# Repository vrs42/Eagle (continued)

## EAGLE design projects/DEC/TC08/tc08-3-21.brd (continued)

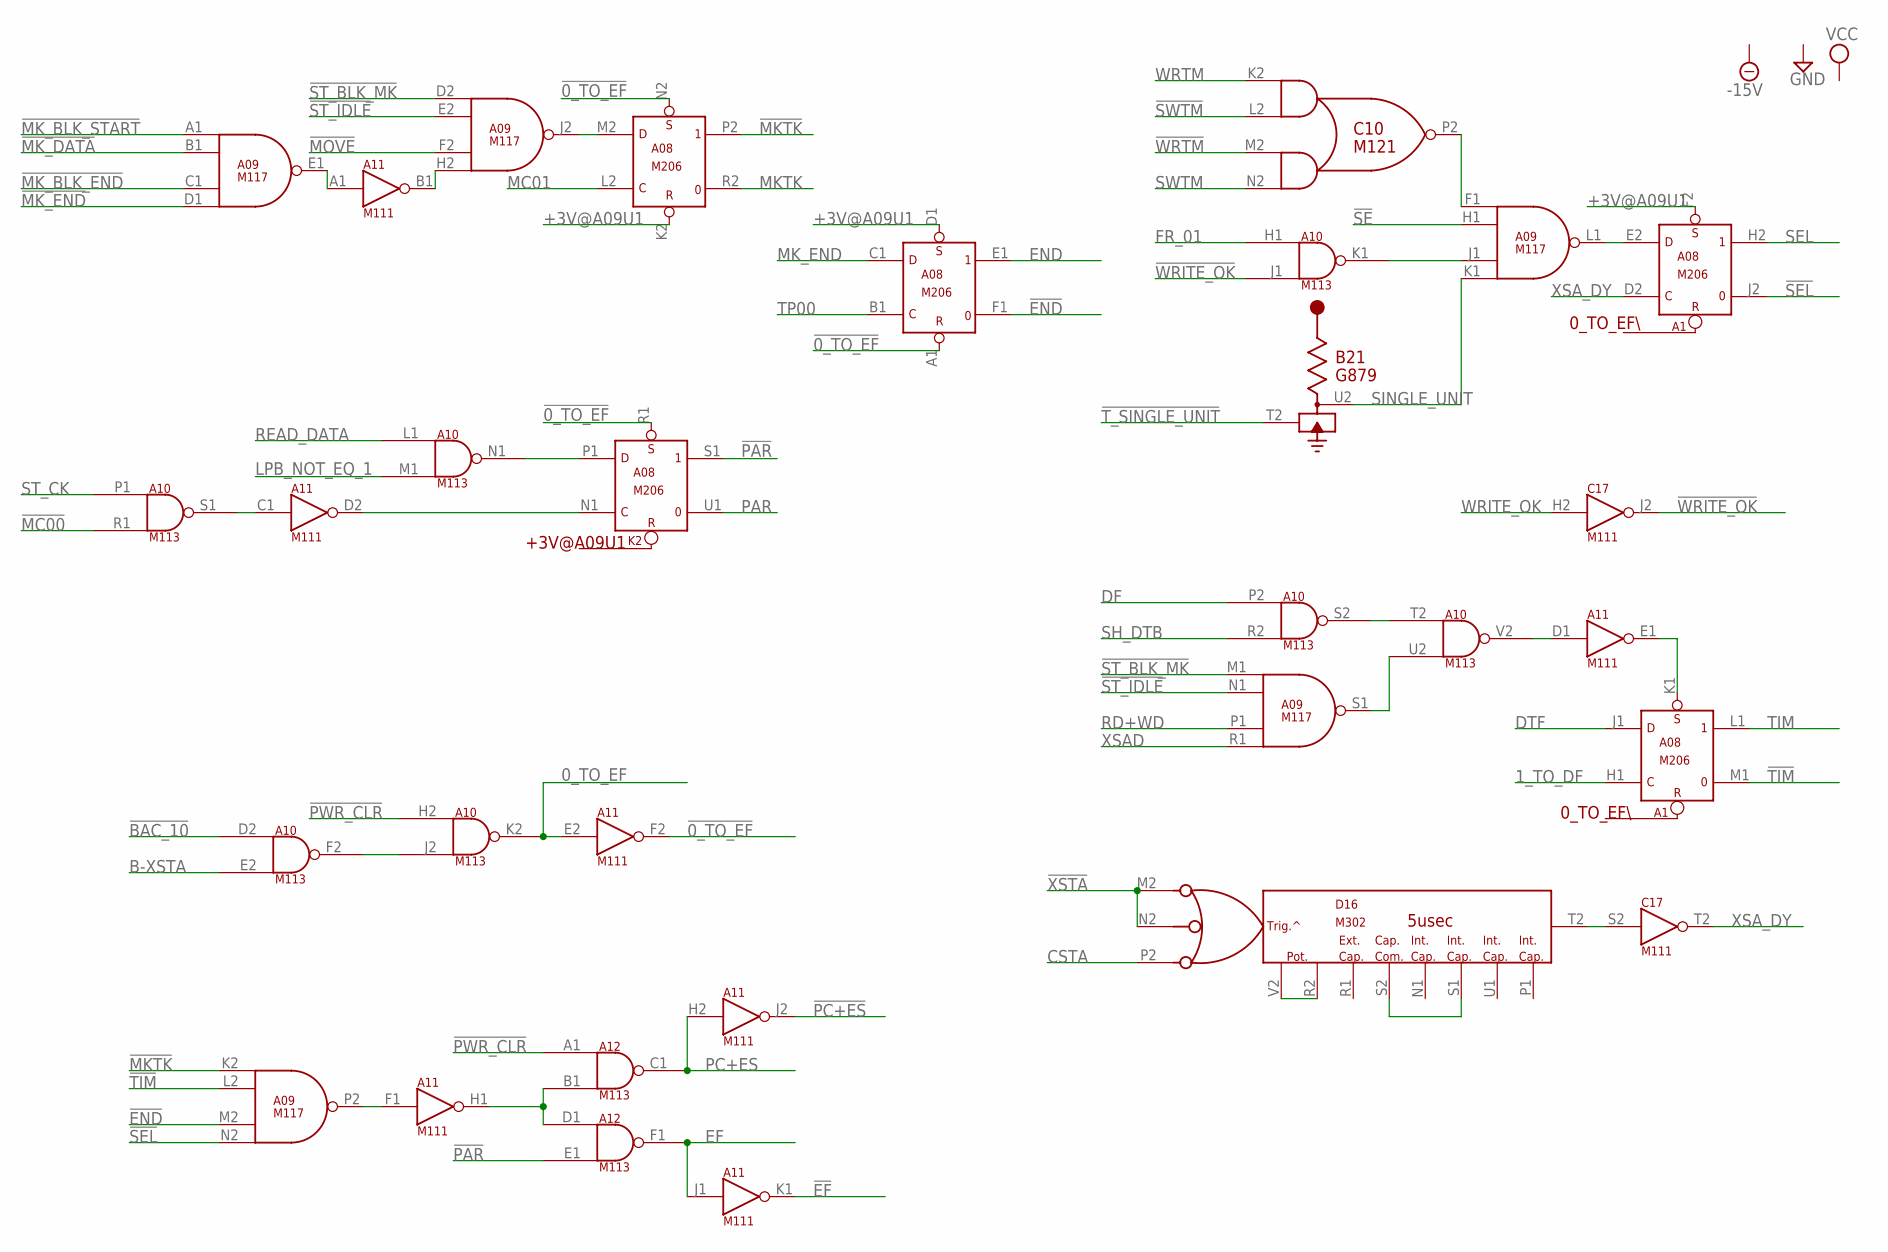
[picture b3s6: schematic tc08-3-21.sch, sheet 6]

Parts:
A08: M206; H807
A09: M117; H807
A10, A12: M113; H807
A11: M111; H807
B21: G879; H807
C10: M121; H807
C17: M111; H807
D16: M302; H807

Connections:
0_TO_EF: A10.K2 (OUT), A11.E2 (IN)
1_TO_DF: A08.H1 (C); also elsewhere on the board
!0_TO_EF: A08.A1 (R), A08.N2 (S), A08.R1 (S), A11.F2 (OUT)
!BAC_10: A10.D2 (IN1); also elsewhere on the board
!EF: A11.K1 (OUT); also elsewhere on the board
!END: A08.F1 (0), A09.M2 (IN3); also elsewhere on the board
!MC00: A10.R1 (IN2); also elsewhere on the board
!MKTK: A08.P2 (1), A09.K2 (IN1); also elsewhere on the board
!MK_BLK_END: A09.C1 (IN3); also elsewhere on the board
!MK_BLK_START: A09.A1 (IN1); also elsewhere on the board
!MK_DATA: A09.B1 (IN2); also elsewhere on the board
!MK_END: A09.D1 (IN4); also elsewhere on the board
!MOVE: A09.F2 (IN3); also elsewhere on the board
!PAR: A08.S1 (1), A12.E1 (IN2); also elsewhere on the board
!PC+ES: A11.J2 (OUT); also elsewhere on the board
!PWR_CLR: A10.H2 (IN1), A12.A1 (IN1); also elsewhere on the board
!SE: A09.H1 (IN2); also elsewhere on the board
!SEL: A08.J2 (0), A09.N2 (IN4); also elsewhere on the board
!ST_BLK_MK: A09.D2 (IN1), A09.M1 (IN1); also elsewhere on the board
!ST_IDLE: A09.E2 (IN2), A09.N1 (IN2); also elsewhere on the board
!SWTM: C10.L2 (IN1B); also elsewhere on the board
!TIM: A08.M1 (0), A09.L2 (IN2); also elsewhere on the board
!T_SINGLE_UNIT: B21.T2 (IN); also elsewhere on the board
!WRITE_OK: A10.J1 (IN2), C17.J2 (OUT)
!WRTM: C10.M2 (IN2A); also elsewhere on the board
!XSTA: D16.M2 (H2), D16.N2 (J2); also elsewhere on the board
+3V@A09U1: A08.D1 (S), A08.F2 (S), A08.K2 (R); also elsewhere on the board
-15V: B21.B2 (-15V); also elsewhere on the board
B-XSTA: A10.E2 (IN2); also elsewhere on the board
CSTA: D16.P2 (K2); also elsewhere on the board
DF: A10.P2 (IN1); also elsewhere on the board
DTF: A08.J1 (D); also elsewhere on the board
EF: A11.J1 (IN), A12.F1 (OUT); also elsewhere on the board
END: A08.E1 (1); also elsewhere on the board
FR_01: A10.H1 (IN1); also elsewhere on the board
GND: A08.C2 (GND), A08.T1 (GND), A09.C2 (GND), A09.T1 (GND), A10.C2 (GND), A10.T1 (GND), A11.C2 (GND), A11.T1 (GND), A12.C2 (GND), A12.T1 (GND), B21.C2 (GND), C10.C2 (GND), C10.T1 (GND), C17.C2 (GND), C17.T1 (GND), D16.C2 (GND), D16.T1 (GND); also elsewhere on the board
LPB_NOT_EQ_1: A10.M1 (IN2); also elsewhere on the board
MC01: A08.L2 (C); also elsewhere on the board
MKTK: A08.R2 (0); also elsewhere on the board
MK_END: A08.C1 (D); also elsewhere on the board
unnamed: C17.S2 (IN), D16.T2 (F2)
unnamed: A09.F1 (IN1), C10.P2 (OUT)
unnamed: A09.J1 (IN3), A10.K1 (OUT)
unnamed: A08.E2 (D), A09.L1 (OUT)
unnamed: A09.E1 (OUT), A11.A1 (IN)
unnamed: A09.H2 (IN4), A11.B1 (OUT)
unnamed: A08.M2 (D), A09.J2 (OUT)
unnamed: A10.S1 (OUT), A11.C1 (IN)
unnamed: A08.P1 (D), A10.N1 (OUT)
unnamed: A08.N1 (C), A11.D2 (OUT)
unnamed: A08.K1 (S), A11.E1 (OUT)
unnamed: A10.V2 (OUT), A11.D1 (IN)
unnamed: A09.S1 (OUT), A10.U2 (IN2)
unnamed: A10.S2 (OUT), A10.T2 (IN1)
unnamed: D16.S1 (H1), D16.S2 (L2)
unnamed: D16.R2 (E2), D16.V2 (D2)
unnamed: A10.F2 (OUT), A10.J2 (IN2)
unnamed: A09.P2 (OUT), A11.F1 (IN)
unnamed: A11.H1 (OUT), A12.B1 (IN2), A12.D1 (IN1)
PAR: A08.U1 (0); also elsewhere on the board
PC+ES: A11.H2 (IN), A12.C1 (OUT)
RD+WD: A09.P1 (IN3); also elsewhere on the board
READ_DATA: A10.L1 (IN1); also elsewhere on the board
SEL: A08.H2 (1); also elsewhere on the board
SH_DTB: A10.R2 (IN2); also elsewhere on the board
SINGLE_UNIT: A09.K1 (IN4), B21.U2 (OUT)
ST_CK: A10.P1 (IN1); also elsewhere on the board
SWTM: C10.N2 (IN2B); also elsewhere on the board
TIM: A08.L1 (1); also elsewhere on the board
TP00: A08.B1 (C); also elsewhere on the board
VCC: A08.A2 (VCC), A09.A2 (VCC), A10.A2 (VCC), A11.A2 (VCC), A12.A2 (VCC), B21.A2 (VCC), C10.A2 (VCC), C17.A2 (VCC), D16.A2 (VCC); also elsewhere on the board
WRITE_OK: C17.H2 (IN); also elsewhere on the board
WRTM: C10.K2 (IN1A); also elsewhere on the board
XSAD: A09.R1 (IN4); also elsewhere on the board
XSA_DY: A08.D2 (C), C17.T2 (OUT); also elsewhere on the board

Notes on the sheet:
5usec
+3V@A09U1
0_TO_EF\\

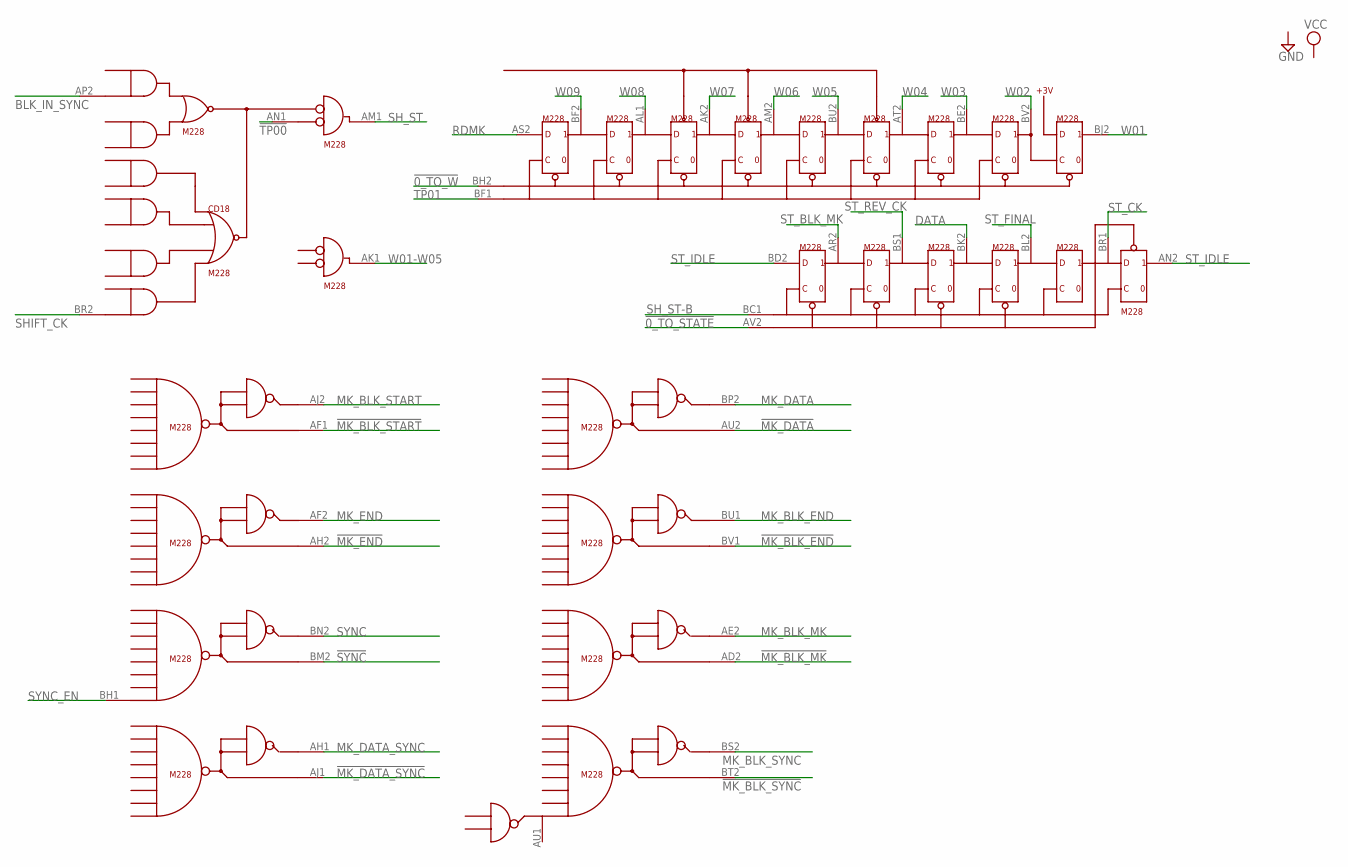
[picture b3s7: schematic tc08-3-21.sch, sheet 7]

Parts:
CD18: M228; H807-2

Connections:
!0_TO_STATE: CD18.AV2; also elsewhere on the board
!0_TO_W: CD18.BH2; also elsewhere on the board
!MK_BLK_END: CD18.BV1; also elsewhere on the board
!MK_BLK_MK: CD18.AD2
!MK_BLK_START: CD18.AF1; also elsewhere on the board
!MK_BLK_SYNC: CD18.BT2
!MK_DATA: CD18.AU2; also elsewhere on the board
!MK_DATA_SYNC: CD18.AJ1
!MK_END: CD18.AH2; also elsewhere on the board
!SYNC: CD18.BM2
!TP00: CD18.AN1; also elsewhere on the board
BLK_IN_SYNC: CD18.AP2; also elsewhere on the board
DATA: CD18.BK2; also elsewhere on the board
GND: CD18.AC2 (GND), CD18.AT1 (GND), CD18.BC2 (GND), CD18.BT1 (GND); also elsewhere on the board
MK_BLK_END: CD18.BU1; also elsewhere on the board
MK_BLK_MK: CD18.AE2; also elsewhere on the board
MK_BLK_START: CD18.AJ2
MK_BLK_SYNC: CD18.BS2
MK_DATA: CD18.BP2
MK_DATA_SYNC: CD18.AH1
MK_END: CD18.AF2; also elsewhere on the board
RDMK: CD18.AS2; also elsewhere on the board
SHIFT_CK: CD18.BR2; also elsewhere on the board
SH_ST: CD18.AM1; also elsewhere on the board
SH_ST-B: CD18.BC1; also elsewhere on the board
ST_BLK_MK: CD18.AR2; also elsewhere on the board
ST_CK: CD18.BR1; also elsewhere on the board
ST_FINAL: CD18.BL2; also elsewhere on the board
ST_IDLE: CD18.AN2, CD18.BD2; also elsewhere on the board
ST_REV_CK: CD18.BS1; also elsewhere on the board
SYNC: CD18.BN2; also elsewhere on the board
SYNC_EN: CD18.BH1; also elsewhere on the board
TP01: CD18.BF1; also elsewhere on the board
VCC: CD18.AA2 (VCC), CD18.BA2 (VCC); also elsewhere on the board
W01: CD18.BJ2; also elsewhere on the board
W01-W05: CD18.AK1
W02: CD18.BV2; also elsewhere on the board
W03: CD18.BE2; also elsewhere on the board
W04: CD18.AT2; also elsewhere on the board
W05: CD18.BU2; also elsewhere on the board
W06: CD18.AM2; also elsewhere on the board
W07: CD18.AK2; also elsewhere on the board
W08: CD18.AL1; also elsewhere on the board
W09: CD18.BF2; also elsewhere on the board

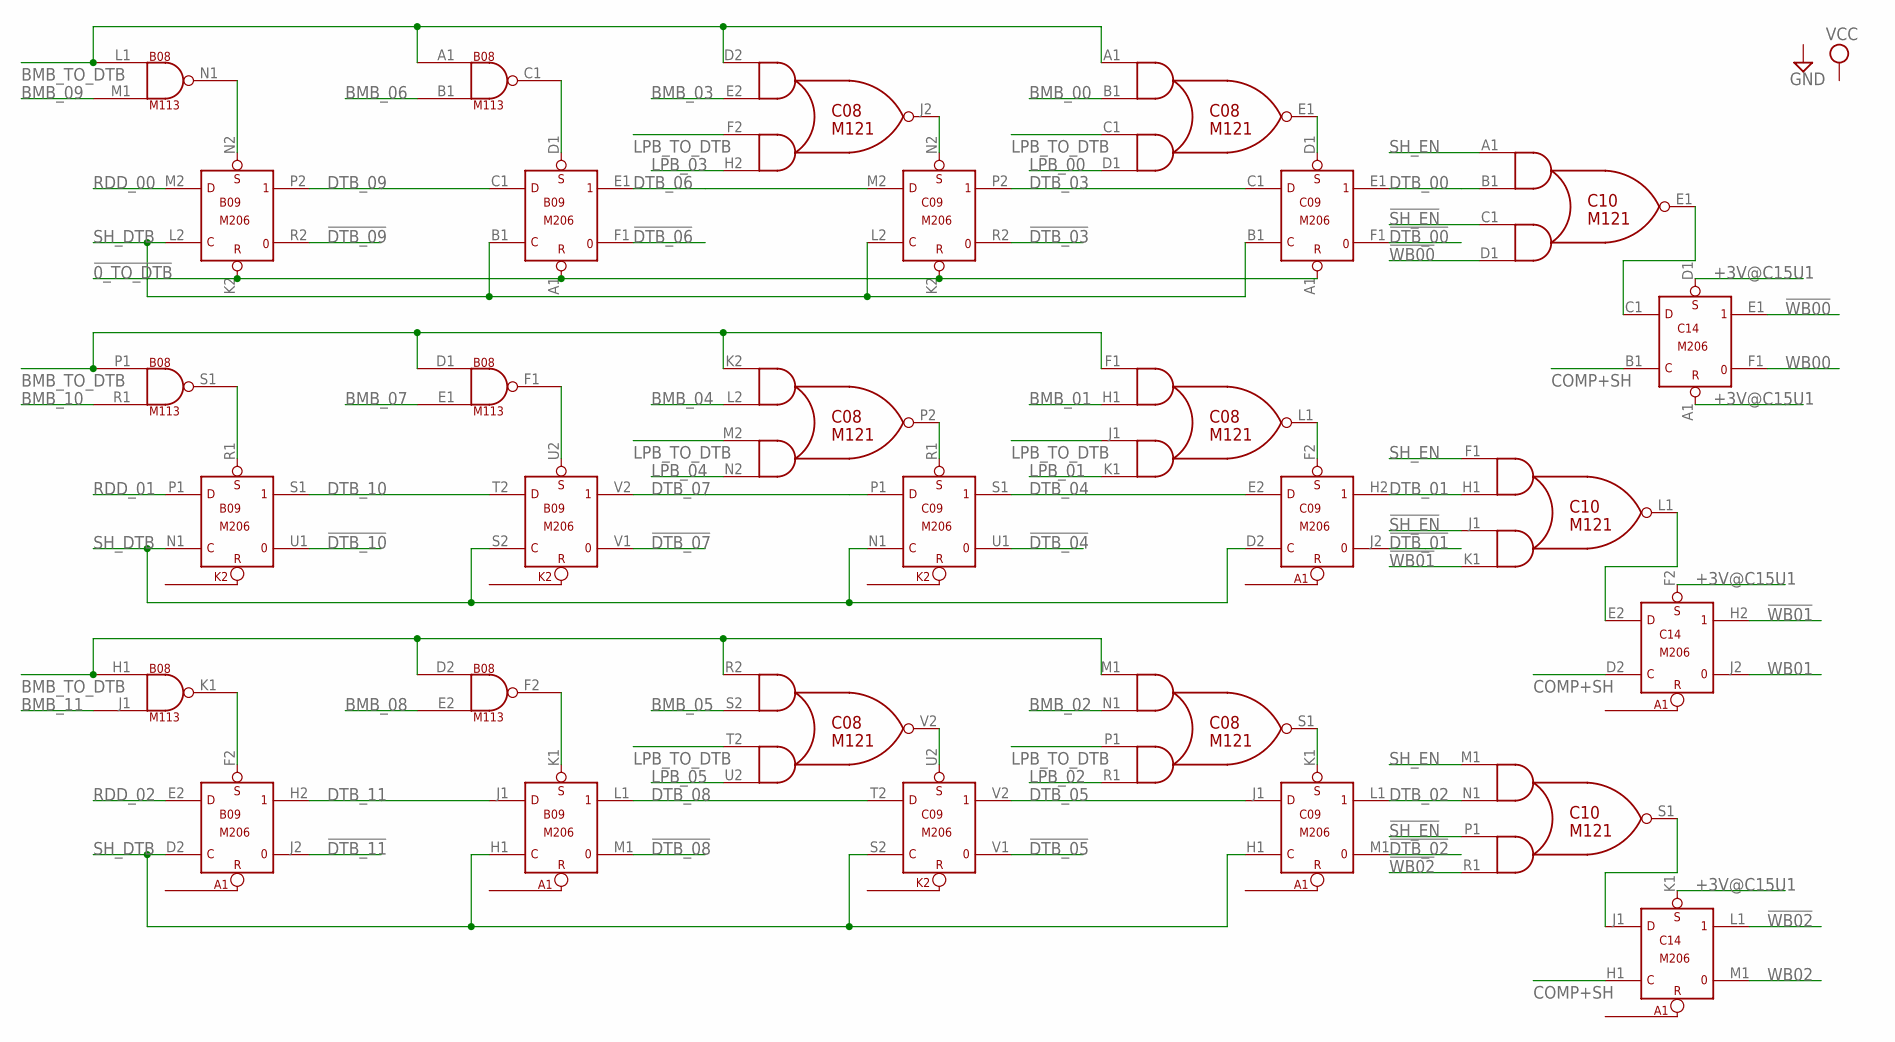
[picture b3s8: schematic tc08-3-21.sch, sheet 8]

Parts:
B08: M113; H807
B09: M206; H807
C08, C10: M121; H807
C09, C14: M206; H807

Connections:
!0_TO_DTB: B09.A1 (R), B09.K2 (R), C09.A1 (R), C09.K2 (R); also elsewhere on the board
!DTB_00: C09.F1 (0); also elsewhere on the board
!DTB_01: C09.J2 (0); also elsewhere on the board
!DTB_02: C09.M1 (0); also elsewhere on the board
!DTB_03: C09.R2 (0); also elsewhere on the board
!DTB_04: C09.U1 (0); also elsewhere on the board
!DTB_05: C09.V1 (0); also elsewhere on the board
!DTB_06: B09.F1 (0); also elsewhere on the board
!DTB_07: B09.V1 (0); also elsewhere on the board
!DTB_08: B09.M1 (0); also elsewhere on the board
!DTB_09: B09.R2 (0); also elsewhere on the board
!DTB_10: B09.U1 (0); also elsewhere on the board
!DTB_11: B09.J2 (0); also elsewhere on the board
!SH_EN: C10.C1 (IN2A), C10.J1 (IN2A), C10.P1 (IN2A); also elsewhere on the board
!WB00: C10.D1 (IN2B), C14.E1 (1); also elsewhere on the board
!WB01: C10.K1 (IN2B), C14.H2 (1); also elsewhere on the board
!WB02: C10.R1 (IN2B), C14.L1 (1); also elsewhere on the board
+3V@C15U1: C14.A1 (R), C14.D1 (S), C14.F2 (S), C14.K1 (S); also elsewhere on the board
BMB_00: C08.B1 (IN1B); also elsewhere on the board
BMB_01: C08.H1 (IN1B); also elsewhere on the board
BMB_02: C08.N1 (IN1B); also elsewhere on the board
BMB_03: C08.E2 (IN1B); also elsewhere on the board
BMB_04: C08.L2 (IN1B); also elsewhere on the board
BMB_05: C08.S2 (IN1B); also elsewhere on the board
BMB_06: B08.B1 (IN2); also elsewhere on the board
BMB_07: B08.E1 (IN2); also elsewhere on the board
BMB_08: B08.E2 (IN2); also elsewhere on the board
BMB_09: B08.M1 (IN2); also elsewhere on the board
BMB_10: B08.R1 (IN2); also elsewhere on the board
BMB_11: B08.J1 (IN2); also elsewhere on the board
BMB_TO_DTB: B08.A1 (IN1), B08.D1 (IN1), B08.D2 (IN1), B08.H1 (IN1), B08.L1 (IN1), B08.P1 (IN1), C08.A1 (IN1A), C08.D2 (IN1A), C08.F1 (IN1A), C08.K2 (IN1A), C08.M1 (IN1A), C08.R2 (IN1A); also elsewhere on the board
COMP+SH: C14.B1 (C), C14.D2 (C), C14.H1 (C); also elsewhere on the board
DTB_00: C09.E1 (1), C10.B1 (IN1B); also elsewhere on the board
DTB_01: C09.H2 (1), C10.H1 (IN1B); also elsewhere on the board
DTB_02: C09.L1 (1), C10.N1 (IN1B); also elsewhere on the board
DTB_03: C09.C1 (D), C09.P2 (1); also elsewhere on the board
DTB_04: C09.E2 (D), C09.S1 (1); also elsewhere on the board
DTB_05: C09.J1 (D), C09.V2 (1); also elsewhere on the board
DTB_06: B09.E1 (1), C09.M2 (D); also elsewhere on the board
DTB_07: B09.V2 (1), C09.P1 (D); also elsewhere on the board
DTB_08: B09.L1 (1), C09.T2 (D); also elsewhere on the board
DTB_09: B09.C1 (D), B09.P2 (1); also elsewhere on the board
DTB_10: B09.S1 (1), B09.T2 (D); also elsewhere on the board
DTB_11: B09.H2 (1), B09.J1 (D); also elsewhere on the board
GND: B08.C2 (GND), B08.T1 (GND), B09.C2 (GND), B09.T1 (GND), C08.C2 (GND), C08.T1 (GND), C09.C2 (GND), C09.T1 (GND), C10.C2 (GND), C10.T1 (GND), C14.C2 (GND), C14.T1 (GND); also elsewhere on the board
LPB_00: C08.D1 (IN2B); also elsewhere on the board
LPB_01: C08.K1 (IN2B); also elsewhere on the board
LPB_02: C08.R1 (IN2B); also elsewhere on the board
LPB_03: C08.H2 (IN2B); also elsewhere on the board
LPB_04: C08.N2 (IN2B); also elsewhere on the board
LPB_05: C08.U2 (IN2B); also elsewhere on the board
LPB_TO_DTB: C08.C1 (IN2A), C08.F2 (IN2A), C08.J1 (IN2A), C08.M2 (IN2A), C08.P1 (IN2A), C08.T2 (IN2A); also elsewhere on the board
unnamed: B08.N1 (OUT), B09.N2 (S)
unnamed: B08.S1 (OUT), B09.R1 (S)
unnamed: B08.K1 (OUT), B09.F2 (S)
unnamed: B08.C1 (OUT), B09.D1 (S)
unnamed: C08.J2 (OUT), C09.N2 (S)
unnamed: B08.F1 (OUT), B09.U2 (S)
unnamed: B08.F2 (OUT), B09.K1 (S)
unnamed: C08.V2 (OUT), C09.U2 (S)
unnamed: C08.P2 (OUT), C09.R1 (S)
unnamed: C08.E1 (OUT), C09.D1 (S)
unnamed: C08.L1 (OUT), C09.F2 (S)
unnamed: C08.S1 (OUT), C09.K1 (S)
unnamed: C10.L1 (OUT), C14.E2 (D)
unnamed: C10.E1 (OUT), C14.C1 (D)
unnamed: C10.S1 (OUT), C14.J1 (D)
RDD_00: B09.M2 (D); also elsewhere on the board
RDD_01: B09.P1 (D); also elsewhere on the board
RDD_02: B09.E2 (D); also elsewhere on the board
SH_DTB: B09.B1 (C), B09.D2 (C), B09.H1 (C), B09.L2 (C), B09.N1 (C), B09.S2 (C), C09.B1 (C), C09.D2 (C), C09.H1 (C), C09.L2 (C), C09.N1 (C), C09.S2 (C); also elsewhere on the board
SH_EN: C10.A1 (IN1A), C10.F1 (IN1A), C10.M1 (IN1A); also elsewhere on the board
VCC: B08.A2 (VCC), B09.A2 (VCC), C08.A2 (VCC), C09.A2 (VCC), C10.A2 (VCC), C14.A2 (VCC); also elsewhere on the board
WB00: C14.F1 (0); also elsewhere on the board
WB01: C14.J2 (0); also elsewhere on the board
WB02: C14.M1 (0); also elsewhere on the board

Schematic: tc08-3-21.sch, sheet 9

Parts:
A09: M117; H807
A11: M111; H807
C10: M121; H807
C11, C15: M113; H807
C12: M115; H807
C13, C17: M111; H807
D08: M207; H807
D09: M121; H807
D10: M119; H807
D12: M627; H807

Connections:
!0_TO_LPB: D08.A1, D08.K2, D12.J2 (OUT)
!C00: C15.J2 (IN2); also elsewhere on the board
!C01: C12.F2 (IN3); also elsewhere on the board
!LPB_00: D08.F1
!LPB_01: D08.M1
!LPB_02: D08.U1
!LPB_03: D08.J2
!LPB_04: D08.R2
!LPB_05: D08.V1
!WR_EN: C11.H2 (IN1), C15.D2 (IN1), C15.H2 (IN1); also elsewhere on the board
C00: C15.E2 (IN2); also elsewhere on the board
DTB_00: D09.D2 (IN1A); also elsewhere on the board
DTB_01: D09.K2 (IN1A); also elsewhere on the board
DTB_02: D09.R2 (IN1A); also elsewhere on the board
GND: A09.C2 (GND), A09.T1 (GND), A11.C2 (GND), A11.T1 (GND), C10.C2 (GND), C10.T1 (GND), C11.C2 (GND), C11.T1 (GND), C12.C2 (GND), C12.T1 (GND), C13.C2 (GND), C13.T1 (GND), C15.C2 (GND), C15.T1 (GND), C17.C2 (GND), C17.T1 (GND), D08.C2 (GND), D08.T1 (GND), D09.C2 (GND), D09.T1 (GND), D10.C2 (GND), D10.T1 (GND), D12.C2 (GND), D12.T1 (GND); also elsewhere on the board
LPB_00: D08.E1, D10.M1 (IN1); also elsewhere on the board
LPB_01: D08.L1, D10.N1 (IN2); also elsewhere on the board
LPB_02: D08.S1, D10.P1 (IN3); also elsewhere on the board
LPB_03: D08.H2, D10.R1 (IN4); also elsewhere on the board
LPB_04: D08.P2, D10.R2 (IN5); also elsewhere on the board
LPB_05: D08.V2, D10.S2 (IN6), D10.T2 (IN7), D10.U2 (IN8); also elsewhere on the board
LPB_NOT_EQ_1: D10.V2 (OUT); also elsewhere on the board
LPB_TO_DTB: A11.T2 (OUT); also elsewhere on the board
MC02: D12.D2 (IN1), D12.E2 (IN2); also elsewhere on the board
MKT: C15.L2 (IN1); also elsewhere on the board
MK_BLK_END: A09.T2 (IN3); also elsewhere on the board
unnamed: D08.C1, D08.D1, D09.E1 (OUT)
unnamed: D08.E2, D08.F2, D09.J2 (OUT)
unnamed: D08.J1, D08.K1, D09.L1 (OUT)
unnamed: D08.P1, D08.R1, D09.S1 (OUT)
unnamed: D08.T2, D08.U2, D09.V2 (OUT)
unnamed: D08.M2, D08.N2, D09.P2 (OUT)
unnamed: C17.U1 (OUT), D08.D2, D08.L2, D08.S2
unnamed: C17.N2 (OUT), D08.B1, D08.H1, D08.N1
unnamed: C10.J2 (OUT), C17.M2 (IN)
unnamed: C10.V2 (OUT), C17.V1 (IN)
unnamed: A09.U2 (IN4), C17.R2 (OUT)
unnamed: A09.V2 (OUT), A11.S2 (IN)
unnamed: C15.N2 (OUT), C17.P2 (IN)
unnamed: C13.S2 (IN), C15.K2 (OUT)
unnamed: C12.H2 (OUT), D12.M2 (IN3), D12.N2 (IN4)
unnamed: C11.K2 (OUT), D12.K2 (IN1), D12.L2 (IN2)
unnamed: C13.P2 (IN), C15.F2 (OUT)
RDD_00: D09.C1 (IN2A), D09.F2 (IN2A); also elsewhere on the board
RDD_01: D09.J1 (IN2A), D09.M2 (IN2A); also elsewhere on the board
RDD_02: D09.P1 (IN2A), D09.T2 (IN2A); also elsewhere on the board
RD_EN_LPB_00-02: C10.D2 (IN1A), C13.T2 (OUT), D09.D1 (IN2B), D09.K1 (IN2B), D09.R1 (IN2B)
RD_EN_LPB_03-05: C10.R2 (IN1A), C13.R2 (OUT), D09.H2 (IN2B), D09.N2 (IN2B), D09.U2 (IN2B)
ST_FINAL: A09.S2 (IN2); also elsewhere on the board
ST_REV_CK: D12.F2 (IN3), D12.H2 (IN4); also elsewhere on the board
TP00_A: C12.E2 (IN2); also elsewhere on the board
TP01: C11.J2 (IN2); also elsewhere on the board
TP01_A: C15.M2 (IN2); also elsewhere on the board
VCC: A09.A2 (VCC), A11.A2 (VCC), C10.A2 (VCC), C11.A2 (VCC), C12.A2 (VCC), C13.A2 (VCC), C15.A2 (VCC), C17.A2 (VCC), D08.A2 (VCC), D09.A2 (VCC), D10.A2 (VCC), D12.A2 (VCC); also elsewhere on the board
WB00: D09.A1 (IN1A); also elsewhere on the board
WB01: D09.F1 (IN1A); also elsewhere on the board
WB02: D09.M1 (IN1A); also elsewhere on the board
WRITE_DATA: A09.R2 (IN1); also elsewhere on the board
WR_EN: C10.H2 (IN2B), C10.U2 (IN2B), C12.D2 (IN1), D09.B1 (IN1B), D09.E2 (IN1B), D09.H1 (IN1B), D09.L2 (IN1B), D09.N1 (IN1B), D09.S2 (IN1B); also elsewhere on the board
XOR_TO_LPB: C10.E2 (IN1B), C10.F2 (IN2A), C10.S2 (IN1B), C10.T2 (IN2A), D12.P2 (OUT)

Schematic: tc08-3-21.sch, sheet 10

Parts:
A18, A20, A21: G888; H807
AB01: G821; H807-2
AB19: W032; H807-2
B06: M111; H807
B18, B20: G888; H807
C06: M111; H807

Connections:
!BAC_00: B06.A1 (IN); also elsewhere on the board
!BAC_01: B06.D1 (IN); also elsewhere on the board
!BAC_02: B06.F1 (IN); also elsewhere on the board
!BAC_03: B06.J1 (IN); also elsewhere on the board
!BAC_04: B06.L1 (IN); also elsewhere on the board
!BAC_05: B06.N1 (IN); also elsewhere on the board
!BAC_06: B06.R1 (IN); also elsewhere on the board
!BAC_07: B06.V1 (IN); also elsewhere on the board
!BAC_08: B06.C1 (IN); also elsewhere on the board
!BAC_09: B06.E2 (IN); also elsewhere on the board
!BAC_10: B06.H2 (IN); also elsewhere on the board
!BAC_11: B06.K2 (IN); also elsewhere on the board
!BMB_00: C06.A1 (IN); also elsewhere on the board
!BMB_01: C06.D1 (IN); also elsewhere on the board
!BMB_02: C06.F1 (IN); also elsewhere on the board
!BMB_03: C06.J1 (IN); also elsewhere on the board
!BMB_04: C06.L1 (IN); also elsewhere on the board
!BMB_05: C06.N1 (IN); also elsewhere on the board
!BMB_06: C06.R1 (IN); also elsewhere on the board
!BMB_07: C06.V1 (IN); also elsewhere on the board
!BMB_08: C06.C1 (IN); also elsewhere on the board
!BMB_09: C06.E2 (IN); also elsewhere on the board
!BMB_10: C06.H2 (IN); also elsewhere on the board
!BMB_11: C06.K2 (IN); also elsewhere on the board
!CK00: A18.N2; also elsewhere on the board
!RDD_00: A21.V2
!RDD_01: B20.V2
!RDD_02: A20.V2
!RDMK: B18.V2
!T_TRK: A18.V2; also elsewhere on the board
!WB00: A21.P2, B18.P2; also elsewhere on the board
!WB01: B20.P2; also elsewhere on the board
!WB02: A20.P2; also elsewhere on the board
+11V: AB01.BM2 (+11V)
-15V: A18.B2 (-15V), A20.B2 (-15V), A21.B2 (-15V), AB01.AB2 (-15V), AB01.AE2 (-15V), AB01.AF2 (-15V), B18.B2 (-15V), B20.B2 (-15V); also elsewhere on the board
BAC_00: B06.B1 (OUT); also elsewhere on the board
BAC_01: B06.E1 (OUT); also elsewhere on the board
BAC_02: B06.H1 (OUT); also elsewhere on the board
BAC_03: B06.K1 (OUT); also elsewhere on the board
BAC_04: B06.M1 (OUT); also elsewhere on the board
BAC_05: B06.P1 (OUT); also elsewhere on the board
BAC_06: B06.S1 (OUT); also elsewhere on the board
BAC_07: B06.U1 (OUT); also elsewhere on the board
BAC_08: B06.D2 (OUT); also elsewhere on the board
BAC_09: B06.F2 (OUT); also elsewhere on the board
BAC_10: B06.J2 (OUT)
BAC_11: B06.L2 (OUT)
BMB_00: C06.B1 (OUT); also elsewhere on the board
BMB_01: C06.E1 (OUT); also elsewhere on the board
BMB_02: C06.H1 (OUT); also elsewhere on the board
BMB_03: C06.K1 (OUT); also elsewhere on the board
BMB_04: C06.M1 (OUT); also elsewhere on the board
BMB_05: C06.P1 (OUT); also elsewhere on the board
BMB_06: C06.S1 (OUT); also elsewhere on the board
BMB_07: C06.U1 (OUT); also elsewhere on the board
BMB_08: C06.D2 (OUT); also elsewhere on the board
BMB_09: C06.F2 (OUT); also elsewhere on the board
BMB_10: C06.J2 (OUT); also elsewhere on the board
BMB_11: C06.L2 (OUT); also elsewhere on the board
CK00: A18.P2; also elsewhere on the board
GND: A18.C2 (GND), A20.C2 (GND), A21.C2 (GND), AB01.AC2 (GND), AB01.AH2 (GND), AB01.AK2 (GND), AB01.AL2 (GND), AB01.AT1 (GND), AB01.BC2 (GND), AB01.BD2 (GND), AB01.BH2 (GND), AB01.BK2 (GND), AB01.BL2 (GND), AB01.BT1 (GND), AB19.AC2 (GND), AB19.AJ2, AB19.AK2 (GND), AB19.AR2, AB19.AS2 (GND), AB19.AT2 (GND), AB19.AU2, AB19.BE2 (GND), AB19.BF2, AB19.BL2 (GND), AB19.BM2, B06.C2 (GND), B06.T1 (GND), B18.C2 (GND), B20.C2 (GND), C06.C2 (GND), C06.T1 (GND); also elsewhere on the board
RDD_00: A21.U2; also elsewhere on the board
RDD_00_NEG: A21.E2, A21.K2, AB19.BP2
RDD_00_POS: A21.D2, A21.J2, AB19.BN2
RDD_01: B20.U2; also elsewhere on the board
RDD_01_NEG: AB19.BJ2, B20.E2, B20.K2
RDD_01_POS: AB19.BH2, B20.D2, B20.J2
RDD_02: A20.U2; also elsewhere on the board
RDD_02_NEG: A20.E2, A20.K2, AB19.BD2
RDD_02_POS: A20.D2, A20.J2, AB19.AV2
RDMK: B18.U2; also elsewhere on the board
RDMK_NEG: AB19.AP2, B18.E2, B18.K2
RDMK_POS: AB19.AN2, B18.D2, B18.J2
TM_EN: A18.R2, B18.R2; also elsewhere on the board
T_TRK: A18.U2; also elsewhere on the board
T_TRK_RD_NEG: A18.E2, A18.K2, AB19.AH2
T_TRK_RD_POS: A18.D2, A18.J2, AB19.AF2
VCC: A18.A2 (VCC), A20.A2 (VCC), A21.A2 (VCC), AB01.AA2 (VCC), AB01.AB1 (VCC), AB01.AC1 (VCC), AB01.AD1 (VCC), AB01.AE1 (VCC), AB01.AF1 (VCC), AB01.AH1 (VCC), AB01.AJ1 (VCC), AB01.AK1 (VCC), AB01.AL1 (VCC), AB01.BA2 (VCC), AB01.BB1 (VCC), AB01.BC1 (VCC), AB01.BD1 (VCC), AB01.BE1 (VCC), B06.A2 (VCC), B18.A2 (VCC), B20.A2 (VCC), C06.A2 (VCC); also elsewhere on the board
WB00: A21.N2, B18.N2; also elsewhere on the board
WB01: B20.N2; also elsewhere on the board
WB02: A20.N2; also elsewhere on the board
WR_EN: A20.R2, A21.R2, B20.R2; also elsewhere on the board

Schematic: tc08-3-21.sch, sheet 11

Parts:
B02, B03, B04, B05: M623; H807
C02, C03: M101; H807

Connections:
76+77: C03.C1 (ENABLE); also elsewhere on the board
!0_TO_AC: B05.H1 (B); also elsewhere on the board
!B-BRK: B02.C1 (C), B02.F2 (C), B02.J1 (C), B02.M2 (C), B02.P1 (C), B02.T2 (C); also elsewhere on the board
!BAC_00: C03.B1 (O1); also elsewhere on the board
!BAC_01: C03.E1 (O2); also elsewhere on the board
!BAC_02: C03.H1 (O3); also elsewhere on the board
!BAC_03: C03.K1 (O4); also elsewhere on the board
!BAC_04: C03.M1 (O5); also elsewhere on the board
!BAC_05: C03.P1 (O6); also elsewhere on the board
!BAC_06: C03.S1 (O7); also elsewhere on the board
!BAC_07: C03.U1 (O8); also elsewhere on the board
!BAC_08: C03.F2 (O9); also elsewhere on the board
!BAC_09: C03.J2 (O10); also elsewhere on the board
!BAC_10: C03.L2 (O11); also elsewhere on the board
!BAC_11: C03.N2 (O12); also elsewhere on the board
!BMB_00: C02.B1 (O1); also elsewhere on the board
!BMB_01: C02.E1 (O2); also elsewhere on the board
!BMB_02: C02.H1 (O3); also elsewhere on the board
!BMB_03: C02.K1 (O4); also elsewhere on the board
!BMB_04: C02.M1 (O5); also elsewhere on the board
!BMB_05: C02.P1 (O6); also elsewhere on the board
!BMB_06: C02.S1 (O7); also elsewhere on the board
!BMB_07: C02.U1 (O8); also elsewhere on the board
!BMB_08: C02.F2 (O9); also elsewhere on the board
!BMB_09: C02.J2 (O10); also elsewhere on the board
!BMB_10: C02.L2 (O11); also elsewhere on the board
!BMB_11: C02.N2 (O12); also elsewhere on the board
!DB_00: B02.D1 (D); also elsewhere on the board
!DB_01: B02.E1 (E); also elsewhere on the board
!DB_02: B02.K1 (D); also elsewhere on the board
!DB_03: B02.L1 (E); also elsewhere on the board
!DB_04: B02.R1 (D); also elsewhere on the board
!DB_05: B02.S1 (E); also elsewhere on the board
!DB_06: B02.H2 (D); also elsewhere on the board
!DB_07: B02.J2 (E); also elsewhere on the board
!DB_08: B02.N2 (D); also elsewhere on the board
!DB_09: B02.P2 (E); also elsewhere on the board
!DB_10: B02.U2 (D); also elsewhere on the board
!DB_11: B02.V2 (E); also elsewhere on the board
!DF: B05.A1 (A); also elsewhere on the board
!DTB_00: B02.A1 (A); also elsewhere on the board
!DTB_01: B02.B1 (B); also elsewhere on the board
!DTB_02: B02.F1 (A); also elsewhere on the board
!DTB_03: B02.H1 (B); also elsewhere on the board
!DTB_04: B02.M1 (A); also elsewhere on the board
!DTB_05: B02.N1 (B); also elsewhere on the board
!DTB_06: B02.D2 (A); also elsewhere on the board
!DTB_07: B02.E2 (B); also elsewhere on the board
!DTB_08: B02.K2 (A); also elsewhere on the board
!DTB_09: B02.L2 (B); also elsewhere on the board
!DTB_10: B02.R2 (A); also elsewhere on the board
!DTB_11: B02.S2 (B); also elsewhere on the board
!DTF: B04.L2 (B); also elsewhere on the board
!EA_00: B05.R1 (D); also elsewhere on the board
!EA_01: B05.S1 (E); also elsewhere on the board
!EA_02: B05.H2 (D); also elsewhere on the board
!EF: B04.A1 (A); also elsewhere on the board
!END: B04.F1 (A); also elsewhere on the board
!ENI: B03.L2 (B); also elsewhere on the board
!FR_00: B03.N1 (B); also elsewhere on the board
!FR_01: B03.D2 (A), B05.E2 (B); also elsewhere on the board
!FR_02: B03.E2 (B); also elsewhere on the board
!FR_03: B03.K2 (A); also elsewhere on the board
!IM_00: B03.D1 (D), B04.D1 (D); also elsewhere on the board
!IM_01: B03.E1 (E), B04.E1 (E); also elsewhere on the board
!IM_02: B03.K1 (D), B04.K1 (D); also elsewhere on the board
!IM_03: B03.L1 (E), B04.L1 (E); also elsewhere on the board
!IM_04: B03.R1 (D), B04.R1 (D); also elsewhere on the board
!IM_05: B03.S1 (E), B04.S1 (E); also elsewhere on the board
!IM_06: B03.H2 (D), B04.H2 (D); also elsewhere on the board
!IM_07: B03.J2 (E), B04.J2 (E); also elsewhere on the board
!IM_08: B03.N2 (D), B04.N2 (D); also elsewhere on the board
!IM_09: B03.P2 (E); also elsewhere on the board
!IM_11: B04.P2 (E); also elsewhere on the board
!INT_RQ: B05.B1 (B); also elsewhere on the board
!MF00: B04.D2 (A), B05.M1 (A); also elsewhere on the board
!MF01: B04.E2 (B), B05.N1 (B); also elsewhere on the board
!MF02: B04.K2 (A), B05.D2 (A); also elsewhere on the board
!MKTK: B04.B1 (B); also elsewhere on the board
!MR00: B03.H1 (B); also elsewhere on the board
!MR01: B03.M1 (A); also elsewhere on the board
!PAR: B04.M1 (A); also elsewhere on the board
!RSTA: B03.C1 (C), B03.F2 (C), B03.J1 (C), B03.M2 (C), B03.P1 (C); also elsewhere on the board
!RSTB: B04.C1 (C), B04.F2 (C), B04.J1 (C), B04.M2 (C), B04.P1 (C); also elsewhere on the board
!SEARCH: B05.K2 (A); also elsewhere on the board
!SEL: B04.H1 (B); also elsewhere on the board
!SKP_RQ: B05.F1 (A); also elsewhere on the board
!TIM: B04.N1 (B); also elsewhere on the board
!USR_00: B03.A1 (A); also elsewhere on the board
!USR_01: B03.B1 (B); also elsewhere on the board
!USR_02: B03.F1 (A); also elsewhere on the board
+3V@C08U1: C02.C1 (ENABLE); also elsewhere on the board
ADDR_ACC: C02.V2 (O15); also elsewhere on the board
GND: B02.C2 (GND), B02.T1 (GND), B02.U1 (GND), B02.V1 (GND), B03.C2 (GND), B03.T1 (GND), B03.U1 (GND), B03.V1 (GND), B04.C2 (GND), B04.T1 (GND), B04.U1 (GND), B04.V1 (GND), B05.C1 (C), B05.C2 (GND), B05.F2 (C), B05.J1 (C), B05.M2 (C), B05.P1 (C), B05.T1 (GND), B05.U1 (GND), B05.V1 (GND), C02.C2 (GND), C02.T1 (GND), C03.C2 (GND), C03.T1 (GND); also elsewhere on the board
I/!O_0_TO_AC: B05.L1 (E); also elsewhere on the board
I/!O_1_TO_CA_INH: B05.N2 (D); also elsewhere on the board
I/!O_ADDR_ACC: C02.U2 (IN15); also elsewhere on the board
I/!O_BRK_RQ: B05.D1 (D); also elsewhere on the board
I/!O_INT_RQ: B05.E1 (E); also elsewhere on the board
I/!O_SKP_RQ: B05.K1 (D); also elsewhere on the board
I/O_BAC_00: C03.A1 (IN1); also elsewhere on the board
I/O_BAC_01: C03.D1 (IN2); also elsewhere on the board
I/O_BAC_02: C03.F1 (IN3); also elsewhere on the board
I/O_BAC_03: C03.J1 (IN4); also elsewhere on the board
I/O_BAC_04: C03.L1 (IN5); also elsewhere on the board
I/O_BAC_05: C03.N1 (IN6); also elsewhere on the board
I/O_BAC_06: C03.R1 (IN7); also elsewhere on the board
I/O_BAC_07: C03.V1 (IN8); also elsewhere on the board
I/O_BAC_08: C03.E2 (IN9); also elsewhere on the board
I/O_BAC_09: C03.H2 (IN10); also elsewhere on the board
I/O_BAC_10: C03.K2 (IN11); also elsewhere on the board
I/O_BAC_11: C03.M2 (IN12); also elsewhere on the board
I/O_BMB_00: C02.A1 (IN1); also elsewhere on the board
I/O_BMB_01: C02.D1 (IN2); also elsewhere on the board
I/O_BMB_02: C02.F1 (IN3); also elsewhere on the board
I/O_BMB_03: C02.J1 (IN4); also elsewhere on the board
I/O_BMB_04: C02.L1 (IN5); also elsewhere on the board
I/O_BMB_05: C02.N1 (IN6); also elsewhere on the board
I/O_BMB_06: C02.R1 (IN7); also elsewhere on the board
I/O_BMB_07: C02.V1 (IN8); also elsewhere on the board
I/O_BMB_08: C02.E2 (IN9); also elsewhere on the board
I/O_BMB_09: C02.H2 (IN10); also elsewhere on the board
I/O_BMB_10: C02.K2 (IN11); also elsewhere on the board
I/O_BMB_11: C02.M2 (IN12); also elsewhere on the board
I/O_DATA_IN: B05.J2 (E); also elsewhere on the board
VCC: B02.A2 (VCC), B03.A2 (VCC), B04.A2 (VCC), B05.A2 (VCC), C02.A2 (VCC), C03.A2 (VCC); also elsewhere on the board
